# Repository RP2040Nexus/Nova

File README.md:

# Nova

Nova is a super tiny [RP2040](https://www.raspberrypi.com/products/rp2040/) board featuring an integrated 7x10 addressable LED matrix. This project aims to provide an easy-to-use platform for creating interactive and visually engaging projects.

## Table of Contents

- [Features](#features)
- [Getting Started](#getting-started)
- [Arduino IDE Installation](#arduino-ide-installation)
- [Pinouts](#pinouts)

## Features

- Compact size: Easy to integrate into various projects
- [RP2040](https://www.raspberrypi.com/products/rp2040/) microcontroller: Powerful and efficient
- Integrated 7x10 addressable LED matrix ([WS2812-1010](https://www.mouser.com/datasheet/2/744/WS2812B_1010_DATASHEET-3314306.pdf?srsltid=AfmBOoo3wt47VzInp2GmgZcu0IhygLrT_vyxBrGF-6aGd_k5DdkaCIo3))

## Getting Started

To get started with Nova, you'll need the following:

- [Nova Board](link_to_Nova_Product_Page)
- [Arduino IDE](https://www.arduino.cc/en/software)
- Compatible power source (USB Type-C, battery, etc.)

## Pinouts

## Arduino IDE Installation

### Adding Nova Board to Arduino IDE

1. **Open Arduino IDE**: Launch the Arduino IDE on your computer.

2. **Open Preferences**: 
   - Go to `File` -> `Preferences` (or `Arduino IDE` -> `Preferences` on macOS).

3. **Add Board URL**:
   - In the Preferences window, find the `Additional Boards Manager URLs` field. 
   - Add the following URL to the field:
     ```
     https://github.com/earlephilhower/arduino-pico/releases/download/global/package_rp2040_index.json
     ```
   - If there are already other URLs, separate them with commas.

4. **Open Boards Manager**:
   - Go to `Tools` -> `Board` -> `Boards Manager`.

5. **Install RP2040 Core**:
   - In the Boards Manager window, type `RP2040` in the search box.
   - Look for `Raspberry Pi Pico/RP2040 by Earle Philhower` and click the `Install` button.

6. **Select the Nova Board**:
   - Once the installation is complete, go to `Tools` -> `Board` and select `Raspberry Pi Pico`.

7. ### Install Required Libraries

- It is recommended to use the **FastLED** library for controlling the LED matrix.

#### Installing FastLED Library

1. **Open Library Manager**:
   - Go to `Sketch` -> `Include Library` -> `Manage Libraries...`.

2. **Search for FastLED**:
   - In the Library Manager window, type `FastLED` in the search bar.

3. **Install FastLED**:
   - Find the **FastLED** library ([Repo](https://github.com/FastLED/FastLED)) and click the `Install` button.
  
#### Using FastLED with Nova

Here’s a basic example of how to use the FastLED library to control a single LED on your Nova board:

```cpp
#include <FastLED.h>

#define LED_PIN     22    // Data pin connected to LED0 (GP22)
#define NUM_LEDS    1      // Total number of LEDs (only LED0)

CRGB leds[NUM_LEDS];

void setup() {
    FastLED.addLeds<WS2812, LED_PIN, GRB>(leds, NUM_LEDS);
    FastLED.setBrightness(10); // Set brightness to 10 out of 255
}

void loop() {
    // Example: Set LED0 to red color
    leds[0] = CRGB::Red;
    FastLED.show();
    delay(1000);
    
    // Example: Turn off LED0
    leds[0] = CRGB::Black;
    FastLED.show();
    delay(1000);
}

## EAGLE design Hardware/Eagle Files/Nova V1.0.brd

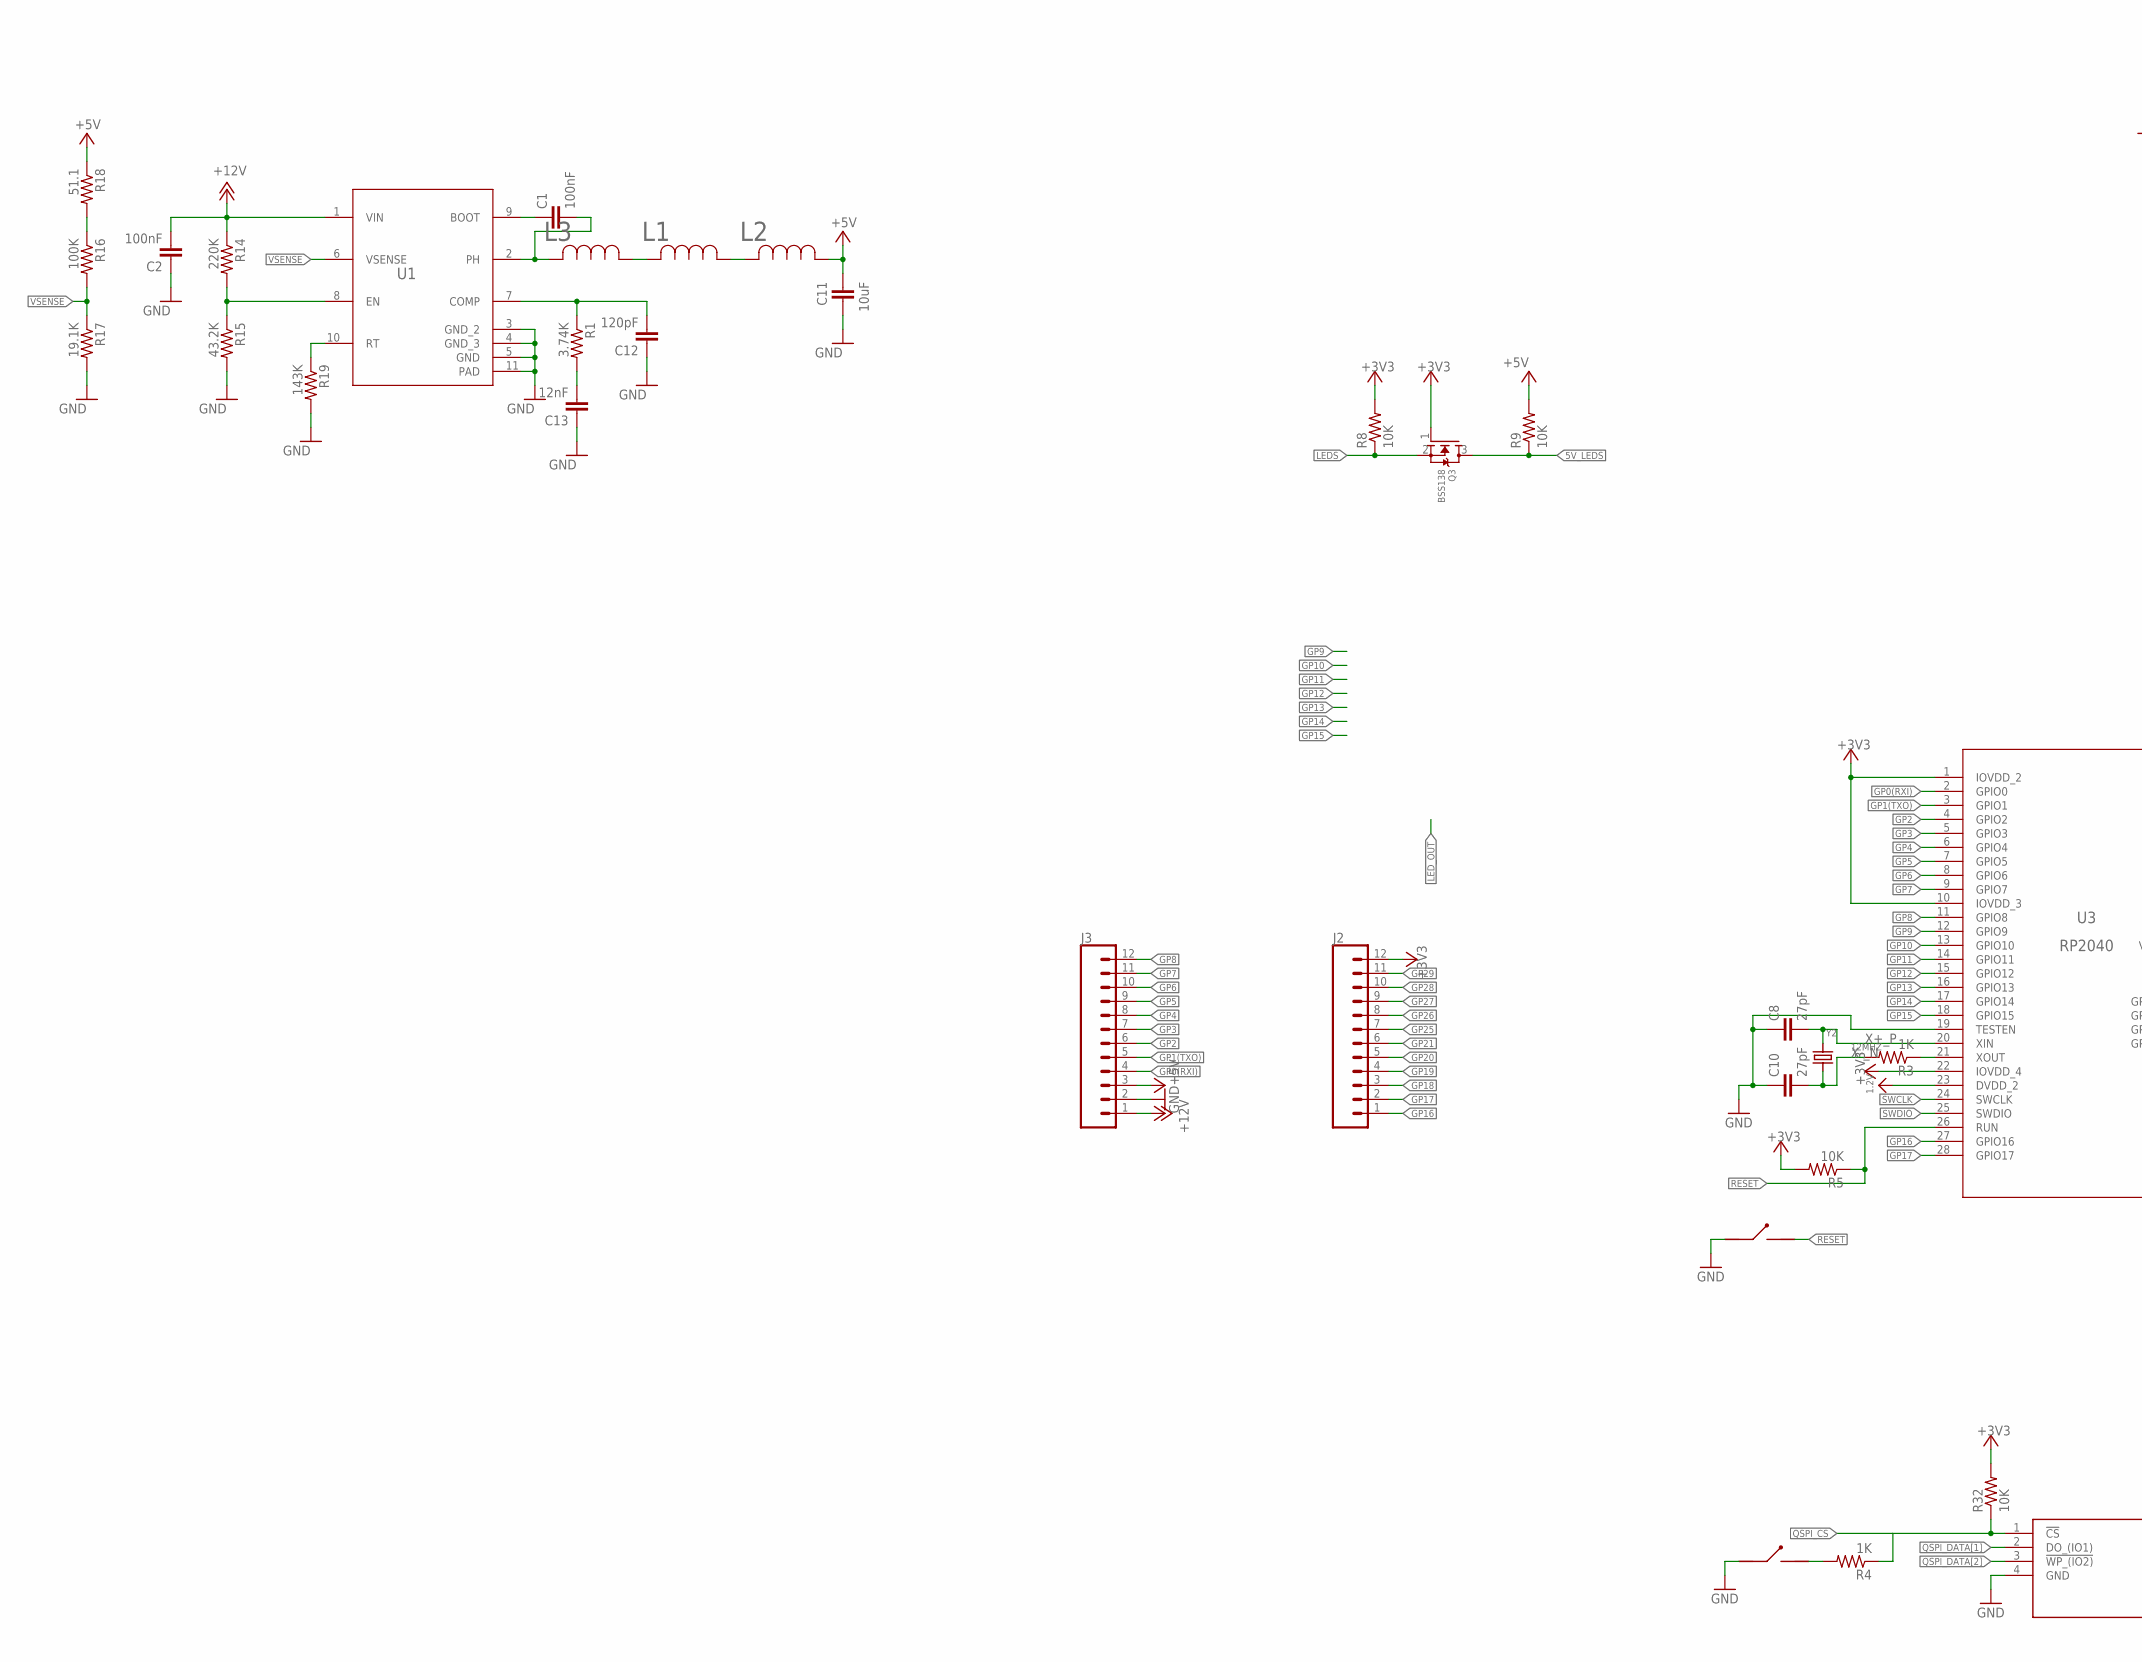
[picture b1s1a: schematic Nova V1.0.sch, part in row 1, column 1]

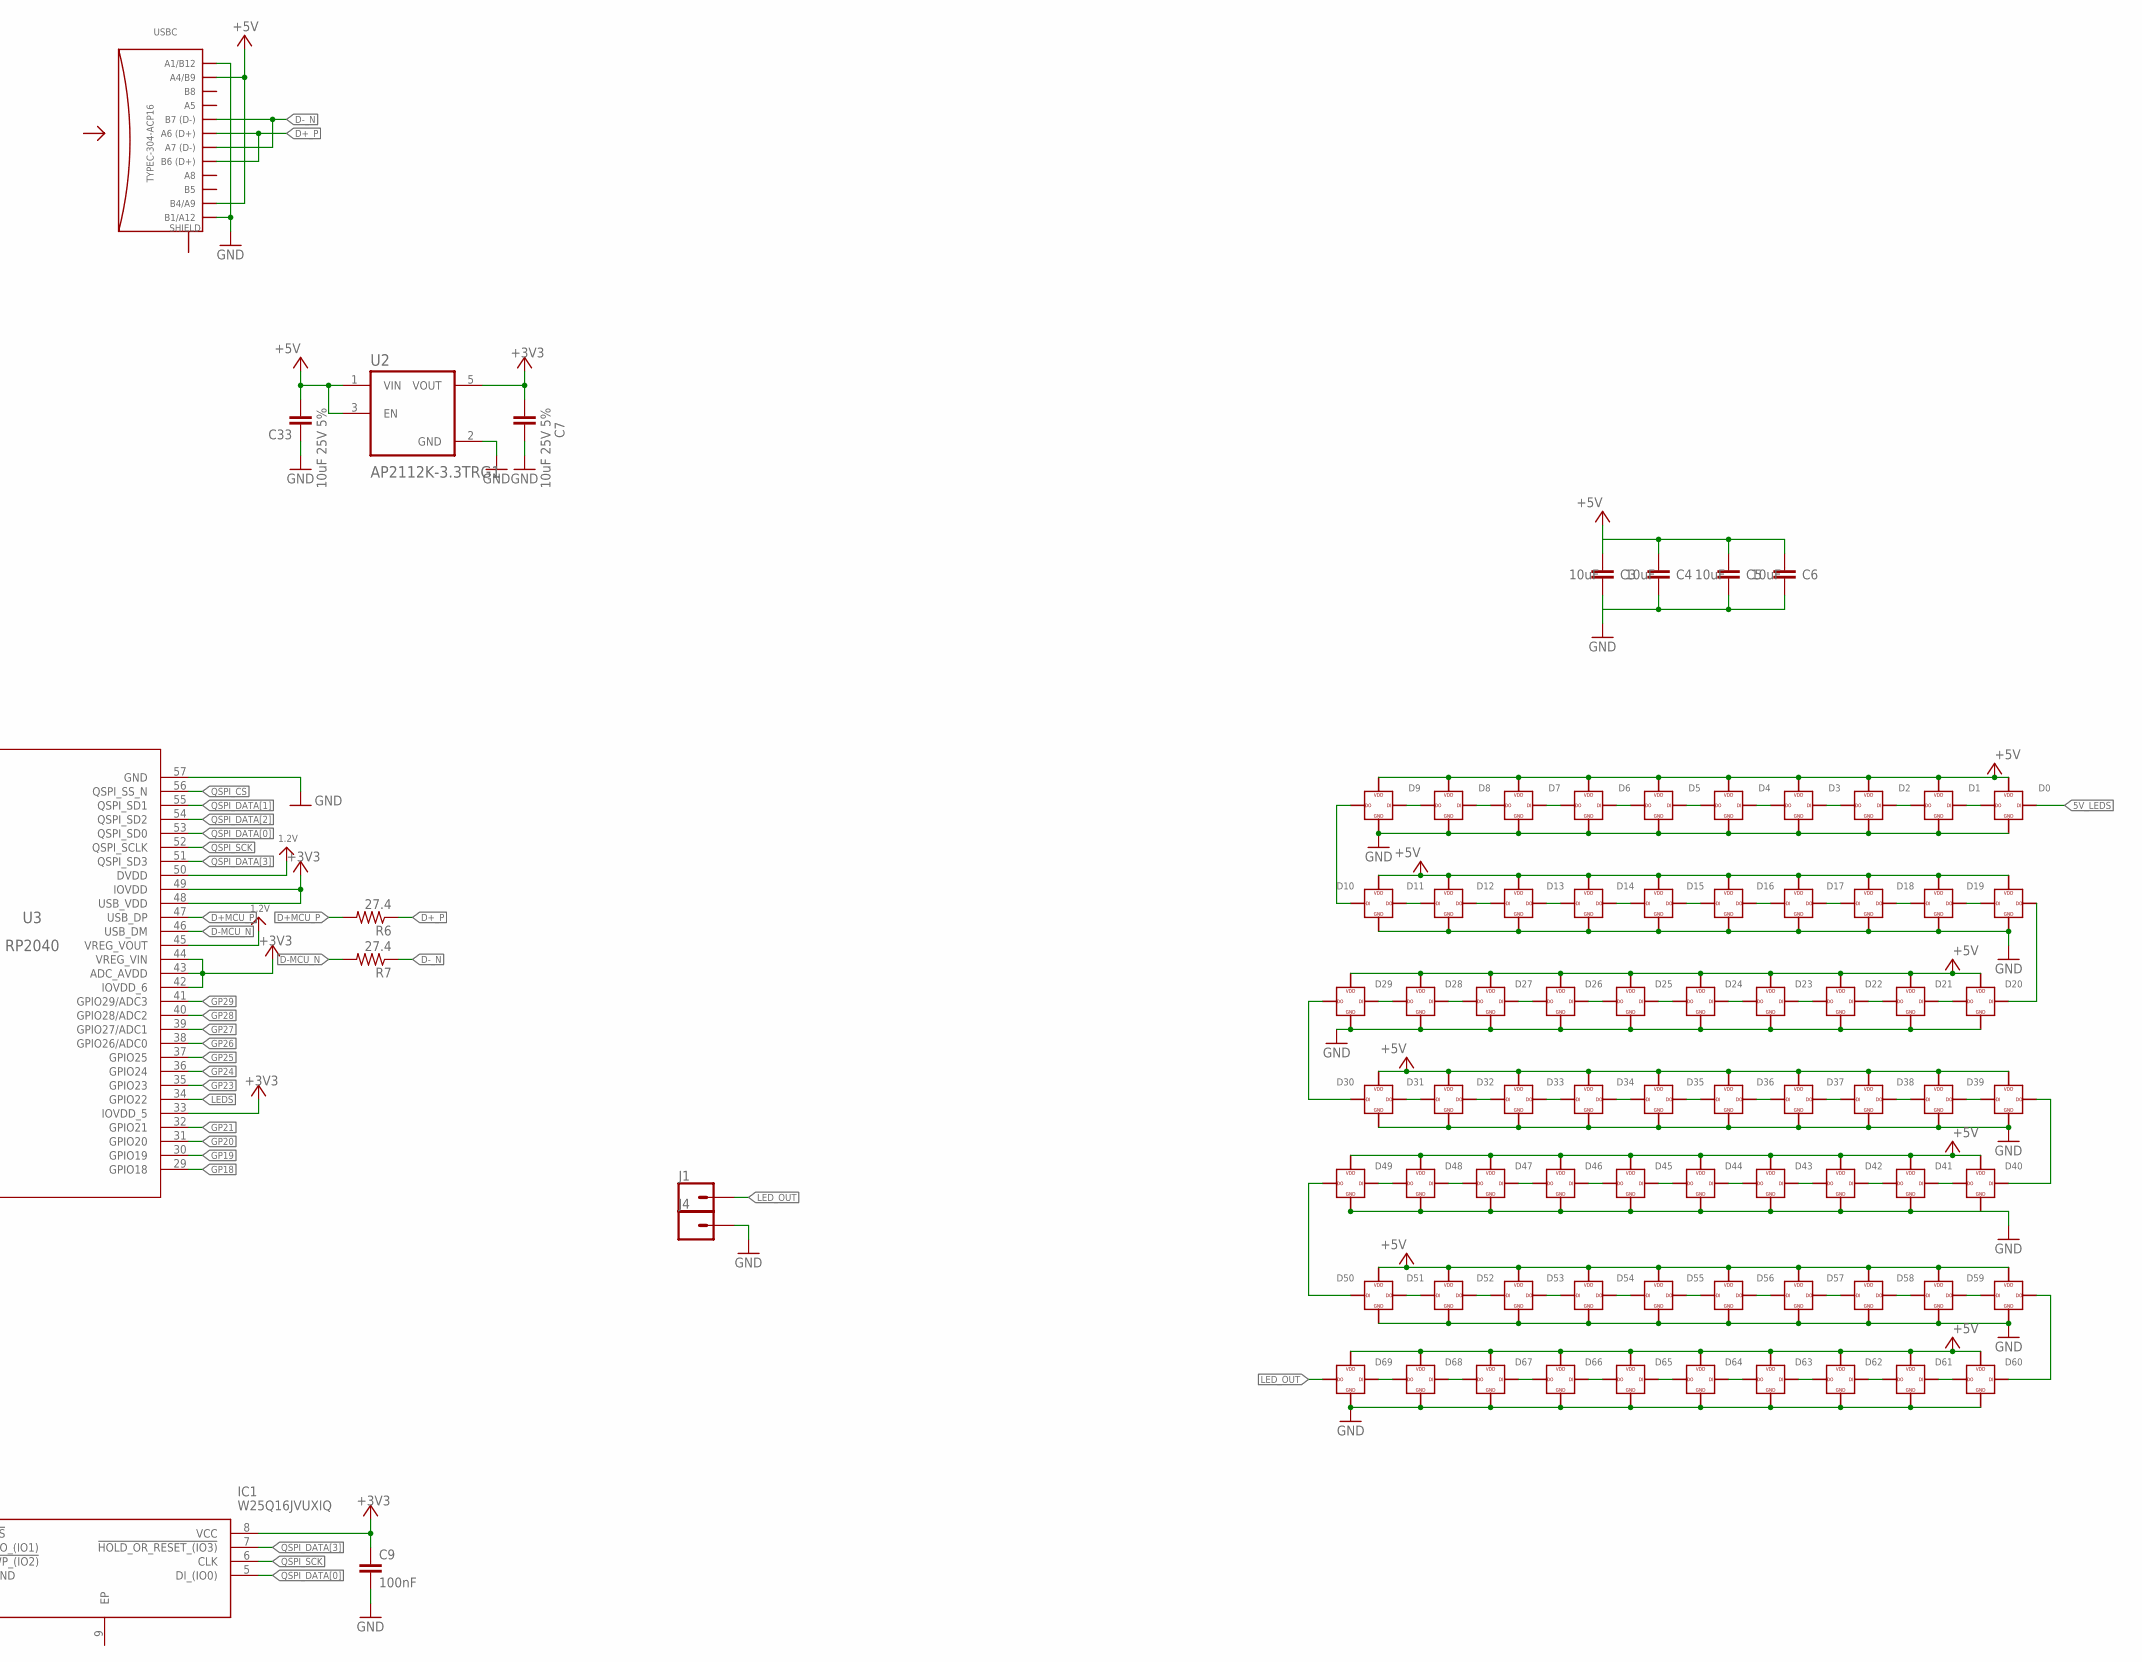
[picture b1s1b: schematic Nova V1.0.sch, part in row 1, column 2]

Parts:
C1, C2, C9: 100nF; 0402-TIGHT
C3, C4, C5, C6, C11: 10uF; C0603
C7, C33: 10uF 25V 5%; C0603
C8, C10: 27pF; 0402-TIGHT
C12: 120pF; 0402-TIGHT
C13: 12nF; 0402-TIGHT
D0, D1, D2, D3, D4, D5, D6, D7, D8, D9, D10, D11, D12, D13, D14, D15, D16, D17, D18, D19, D20, D21, D22, D23, D24, D25, D26, D27, D28, D29, D30, D31, D32, D33, D34, D35, D36, D37, D38, D39, D40, D41, D42, D43, D44, D45, D46, D47, D48, D49, D50, D51, D52, D53, D54, D55, D56, D57, D58, D59, D60, D61, D62, D63, D64, D65, D66, D67, D68, D69: XL-1010RGBC-WS2812B
IC1: W25Q16JVUXIQ; SON50P300X200X60-9N
J1, J4: CONN_01; 1X01
J2, J3: CONN_12; 1X12
L1, L2, L3: MLP2520S4R7MT0S1IND_2520_TDK-L; IND_2520_TDK-L
Q3: BSS138; SOT23
R1: 3.74K; R0402
R3, R4: 1K; R0402
R5, R8, R9, R32: 10K; R0402
R6, R7: 27.4; R0402
R14: 220K; R0402
R15: 43.2K; R0402
R16: 100K; R0402
R17: 19.1K; R0402
R18: 51.1; R0402
R19: 143K; R0402
S1, S2: B3U-1000P
U1: TPS54335ADRCRDRC0010J_NV; DRC0010J_NV
U2: AP2112K-3.3TRG1; SOT95P285X140-5N
U3: RP2040; IC57_RP2040
USBC: TYPEC-304-ACP16
Y2: 12MHZ; CRYSTAL_2.5X2

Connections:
1.2V: U3.23 (DVDD_2), U3.45 (VREG_VOUT), U3.50 (DVDD)
5V_LEDS: D0.4, Q3.3 (D), R9.1
+3V3: C7.2, C9.1, IC1.8 (VCC), J2.12, Q3.1 (G), R5.2, R8.2, R32.2, U2.5 (VOUT), U3.1 (IOVDD_2), U3.10 (IOVDD_3), U3.22 (IOVDD_4), U3.33 (IOVDD_5), U3.42 (IOVDD_6), U3.43 (ADC_AVDD), U3.44 (VREG_VIN), U3.48 (USB_VDD), U3.49 (IOVDD)
+5V: C3.1, C4.1, C5.1, C6.1, C11.2, C33.2, D0.2, D1.2, D2.2, D3.2, D4.2, D5.2, D6.2, D7.2, D8.2, D9.2, D10.2, D11.2, D12.2, D13.2, D14.2, D15.2, D16.2, D17.2, D18.2, D19.2, D20.2, D21.2, D22.2, D23.2, D24.2, D25.2, D26.2, D27.2, D28.2, D29.2, D30.2, D31.2, D32.2, D33.2, D34.2, D35.2, D36.2, D37.2, D38.2, D39.2, D40.2, D41.2, D42.2, D43.2, D44.2, D45.2, D46.2, D47.2, D48.2, D49.2, D50.2, D51.2, D52.2, D53.2, D54.2, D55.2, D56.2, D57.2, D58.2, D59.2, D60.2, D61.2, D62.2, D63.2, D64.2, D65.2, D66.2, D67.2, D68.2, D69.2, J3.3, L2.1, R9.2, R18.1, U2.1 (VIN), U2.3 (EN), USBC.A4/B9, USBC.B4/A9
+12V: C2.2, J3.1, R14.1, U1.1 (VIN)
D+MCU_P: R6.2, U3.47 (USB_DP)
D+_P: R6.1, USBC.A6, USBC.B6
D-MCU_N: R7.2, U3.46 (USB_DM)
D-_N: R7.1, USBC.A7, USBC.B7
GND: C2.1, C3.2, C4.2, C5.2, C6.2, C7.1, C8.1, C9.2, C10.1, C11.1, C12.1, C13.1, C33.1, D0.3, D1.3, D2.3, D3.3, D4.3, D5.3, D6.3, D7.3, D8.3, D9.3, D10.3, D11.3, D12.3, D13.3, D14.3, D15.3, D16.3, D17.3, D18.3, D19.3, D20.3, D21.3, D22.3, D23.3, D24.3, D25.3, D26.3, D27.3, D28.3, D29.3, D30.3, D31.3, D32.3, D33.3, D34.3, D35.3, D36.3, D37.3, D38.3, D39.3, D40.3, D41.3, D42.3, D43.3, D44.3, D45.3, D46.3, D47.3, D48.3, D49.3, D50.3, D51.3, D52.3, D53.3, D54.3, D55.3, D56.3, D57.3, D58.3, D59.3, D60.3, D61.3, D62.3, D63.3, D64.3, D65.3, D66.3, D67.3, D68.3, D69.3, IC1.4 (GND), J3.2, J4.1, R15.2, R17.2, R19.2, S1.1, S2.1, U1.3 (GND_2), U1.4 (GND_3), U1.5 (GND), U1.11 (PAD), U2.2 (GND), U3.19 (TESTEN), U3.57 (GND), USBC.A1/B12, USBC.B1/A12
GP0(RXI): J3.4, U3.2 (GPIO0)
GP1(TXO): J3.5, U3.3 (GPIO1)
GP2: J3.6, U3.4 (GPIO2)
GP3: J3.7, U3.5 (GPIO3)
GP4: J3.8, U3.6 (GPIO4)
GP5: J3.9, U3.7 (GPIO5)
GP6: J3.10, U3.8 (GPIO6)
GP7: J3.11, U3.9 (GPIO7)
GP8: J3.12, U3.11 (GPIO8)
GP9: U3.12 (GPIO9)
GP10: U3.13 (GPIO10)
GP11: U3.14 (GPIO11)
GP12: U3.15 (GPIO12)
GP13: U3.16 (GPIO13)
GP14: U3.17 (GPIO14)
GP15: U3.18 (GPIO15)
GP16: J2.1, U3.27 (GPIO16)
GP17: J2.2, U3.28 (GPIO17)
GP18: J2.3, U3.29 (GPIO18)
GP19: J2.4, U3.30 (GPIO19)
GP20: J2.5, U3.31 (GPIO20)
GP21: J2.6, U3.32 (GPIO21)
GP23: U3.35 (GPIO23)
GP24: U3.36 (GPIO24)
GP25: J2.7, U3.37 (GPIO25)
GP26: J2.8, U3.38 (GPIO26/ADC0)
GP27: J2.9, U3.39 (GPIO27/ADC1)
GP28: J2.10, U3.40 (GPIO28/ADC2)
GP29: J2.11, U3.41 (GPIO29/ADC3)
LEDS: Q3.2 (S), R8.1, U3.34 (GPIO22)
LED_OUT: D69.1, J1.1
unnamed: D0.1, D1.4
unnamed: D1.1, D2.4
unnamed: D2.1, D3.4
unnamed: D3.1, D4.4
unnamed: D4.1, D5.4
unnamed: D5.1, D6.4
unnamed: D6.1, D7.4
unnamed: D7.1, D8.4
unnamed: D8.1, D9.4
unnamed: D9.1, D10.4
unnamed: D10.1, D11.4
unnamed: D11.1, D12.4
unnamed: D12.1, D13.4
unnamed: D13.1, D14.4
unnamed: D14.1, D15.4
unnamed: D15.1, D16.4
unnamed: D16.1, D17.4
unnamed: D17.1, D18.4
unnamed: D18.1, D19.4
unnamed: D19.1, D20.4
unnamed: D20.1, D21.4
unnamed: D21.1, D22.4
unnamed: D22.1, D23.4
unnamed: D23.1, D24.4
unnamed: D24.1, D25.4
unnamed: D25.1, D26.4
unnamed: D26.1, D27.4
unnamed: D27.1, D28.4
unnamed: D28.1, D29.4
unnamed: D29.1, D30.4
unnamed: D30.1, D31.4
unnamed: D31.1, D32.4
unnamed: D32.1, D33.4
unnamed: D33.1, D34.4
unnamed: D34.1, D35.4
unnamed: D35.1, D36.4
unnamed: D36.1, D37.4
unnamed: D37.1, D38.4
unnamed: D38.1, D39.4
unnamed: D39.1, D40.4
unnamed: D40.1, D41.4
unnamed: D41.1, D42.4
unnamed: D42.1, D43.4
unnamed: D43.1, D44.4
unnamed: D44.1, D45.4
unnamed: D45.1, D46.4
unnamed: D46.1, D47.4
unnamed: D47.1, D48.4
unnamed: D48.1, D49.4
unnamed: D49.1, D50.4
unnamed: D50.1, D51.4
unnamed: D51.1, D52.4
unnamed: D52.1, D53.4
unnamed: D53.1, D54.4
unnamed: D54.1, D55.4
unnamed: D55.1, D56.4
unnamed: D56.1, D57.4
unnamed: D57.1, D58.4
unnamed: D58.1, D59.4
unnamed: D59.1, D60.4
unnamed: D60.1, D61.4
unnamed: D61.1, D62.4
unnamed: D62.1, D63.4
unnamed: D63.1, D64.4
unnamed: D64.1, D65.4
unnamed: D65.1, D66.4
unnamed: D66.1, D67.4
unnamed: D67.1, D68.4
unnamed: D68.1, D69.4
unnamed: R3.1, U3.21 (XOUT)
unnamed: R4.2, S1.2
unnamed: C1.1, U1.9 (BOOT)
unnamed: L1.2, L3.1
unnamed: L1.1, L2.2
unnamed: C13.2, R1.2
unnamed: C12.2, R1.1, U1.7 (COMP)
unnamed: R14.2, R15.1, U1.8 (EN)
unnamed: R16.1, R18.2
unnamed: R19.1, U1.10 (RT)
PH: C1.2, L3.2, U1.2 (PH)
QSPI_CS: IC1.1 (!CS), R4.1, R32.1, U3.56 (QSPI_SS_N)
QSPI_DATA[0]: IC1.5 (DI_(IO0)), U3.53 (QSPI_SD0)
QSPI_DATA[1]: IC1.2 (DO_(IO1)), U3.55 (QSPI_SD1)
QSPI_DATA[2]: IC1.3 (!WP_(IO2)), U3.54 (QSPI_SD2)
QSPI_DATA[3]: IC1.7 (!HOLD_OR_RESET_(IO3)), U3.51 (QSPI_SD3)
QSPI_SCK: IC1.6 (CLK), U3.52 (QSPI_SCLK)
RESET: R5.1, S2.2, U3.26 (RUN)
SWCLK: U3.24 (SWCLK)
SWDIO: U3.25 (SWDIO)
VSENSE: R16.2, R17.1, U1.6 (VSENSE)
X+_P: C8.2, U3.20 (XIN), Y2.3 (2)
X-_N: C10.2, R3.2, Y2.1

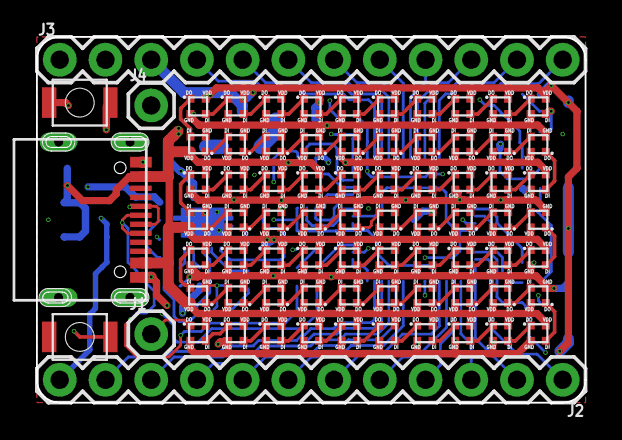
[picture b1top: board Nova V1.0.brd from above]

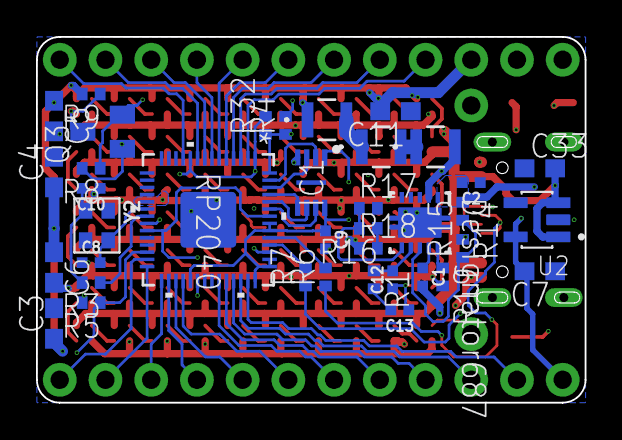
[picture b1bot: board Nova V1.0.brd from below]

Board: 4 copper layers, 30.5 x 20.3 mm, 115 parts (38 on the bottom side), 122 nets.

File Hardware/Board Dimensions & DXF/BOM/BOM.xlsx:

Comment | Designator | Footprint | Manufacturer Part #
Miltilayer Ceramic Capacitor 100nF | C1,C2,C9 | 0402 | CL05B104KB54PNC
Miltilayer Ceramic Capacitor 10uF | C3,C4,C5,C6,C7,C11,C33 | 0603 | GRM188R6YA106MA73D
Miltilayer Ceramic Capacitor 27pF | C8,C10 | 0402 | CC0402JRNPO9BN270
Miltilayer Ceramic Capacitor 120pF | C12 | 0402 | CC0402JRNPO9BN121
Miltilayer Ceramic Capacitor 12nF | C13 | 0402 | GRM155R71H123KA12D
SMD,1x1mm RGB LEDs(Built-in IC) ROHS | D1,D2,D3,D4,D5,D6,D7,D8,D9,D10,D11,D12,D13,D14,D15,D16,D17,D18,D19,D20,D21,D22,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 | SMD,1x1mm | XL-1010RGBC-WS2812B
USON-8-EP(2x3) NOR FLASH ROHS | IC1 | USON-8-EP(2x3) | W25Q16JVUXIQ
1A 4.7uH ±20% 130mΩ 1008 Inductors (SMD) ROHS | L1,L2,L3 | 1008 | MLP2520S4R7MT0S1
50V 220mA 3.5Ω@10V,220mA 360mW 1.5V@1mA 1PCSNChannel SOT-23 MOSFETs ROHS | Q3 | SOT-23 | BSS138
SMD Chip Resistor 3.74K | R1 | 0402 | 0402WGF3741TCE
SMD Chip Resistor 1K | R3,R4 | 0402 | 0402WGF1001TCE
SMD Chip Resistor 10K | R5,R8,R9,R32 | 0402 | 0402WGF1002TCE
SMD Chip Resistor 27.4 | R6,R7 | 0402 | ARG02FTC27R4
SMD Chip Resistor 220K | R14 | 0402 | RC0402FR-07220KL
SMD Chip Resistor 43.2K | R15 | 0402 | RT0402FRE0743K2L
SMD Chip Resistor 100K | R16 | 0402 | RC0402FR-07100KL
SMD Chip Resistor 19.1K | R17 | 0402 | 0402WGF1912TCE
SMD Chip Resistor 51.1 | R18 | 0402 | SCR0402F51R1
SMD Chip Resistor 143K | R19 | 0402 | FRC0402F1433TS
2.5mm 1.6mm Round Button 50mA Standing paste 3mm SPST 153gf 12V SMD,2.5x3mm Tac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 | S1 | SMD,2.5x3mm | B3U-1000P
Step-down type Adjustable 800mV~24V 3A 4.5V~28V VSON-10-EP(3x3) DC-DC Converter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 | U1 | VSON-10-EP(3x3) | TPS54335ADRCR
65dB@(100Hz,1kHz) 600mA Fixed 3.3V Positive electrode 6V SOT-25-5 Voltage Regul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 | U2 | SOT-25-5 | AP2112K-3.3TRG1
264KB 30 133MHz LQFN-56(7x7) Microcontrollers (MCU/MPU/SOC) ROHS | U3 | LQFN-56(7x7) | RP2040
TYPEC-304-ACP16 | USBC | TYPEC-304-ACP16 | TYPEC-304-ACP16
12MHz SMD Crystal Resonator 18pF 150Ω ±10ppm ±30ppm -40℃~+85℃ SMD2520-4P Crysta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 | Y2 | SMD2520-4P | 2TJ412000XYGBC

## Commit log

2024-11-02 Create LICENSE
2024-11-21 Replaced the old Nova pinouts with the new ones.
2024-11-21 Created a new Illustrations files to replace the old one
2024-11-21 Create Illustrations
2024-11-21 Add files via upload
    Pinouts Updated

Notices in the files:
parts and their libraries:
SparkFun-Connectors: Licensing: Creative Commons ShareAlike 4.0 International - https://creativecommons.org/licenses/by-sa/4.0
microbuilder: This work is placed in the public domain, and may be freely used for commercial and non-commercial work with the following conditions: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
